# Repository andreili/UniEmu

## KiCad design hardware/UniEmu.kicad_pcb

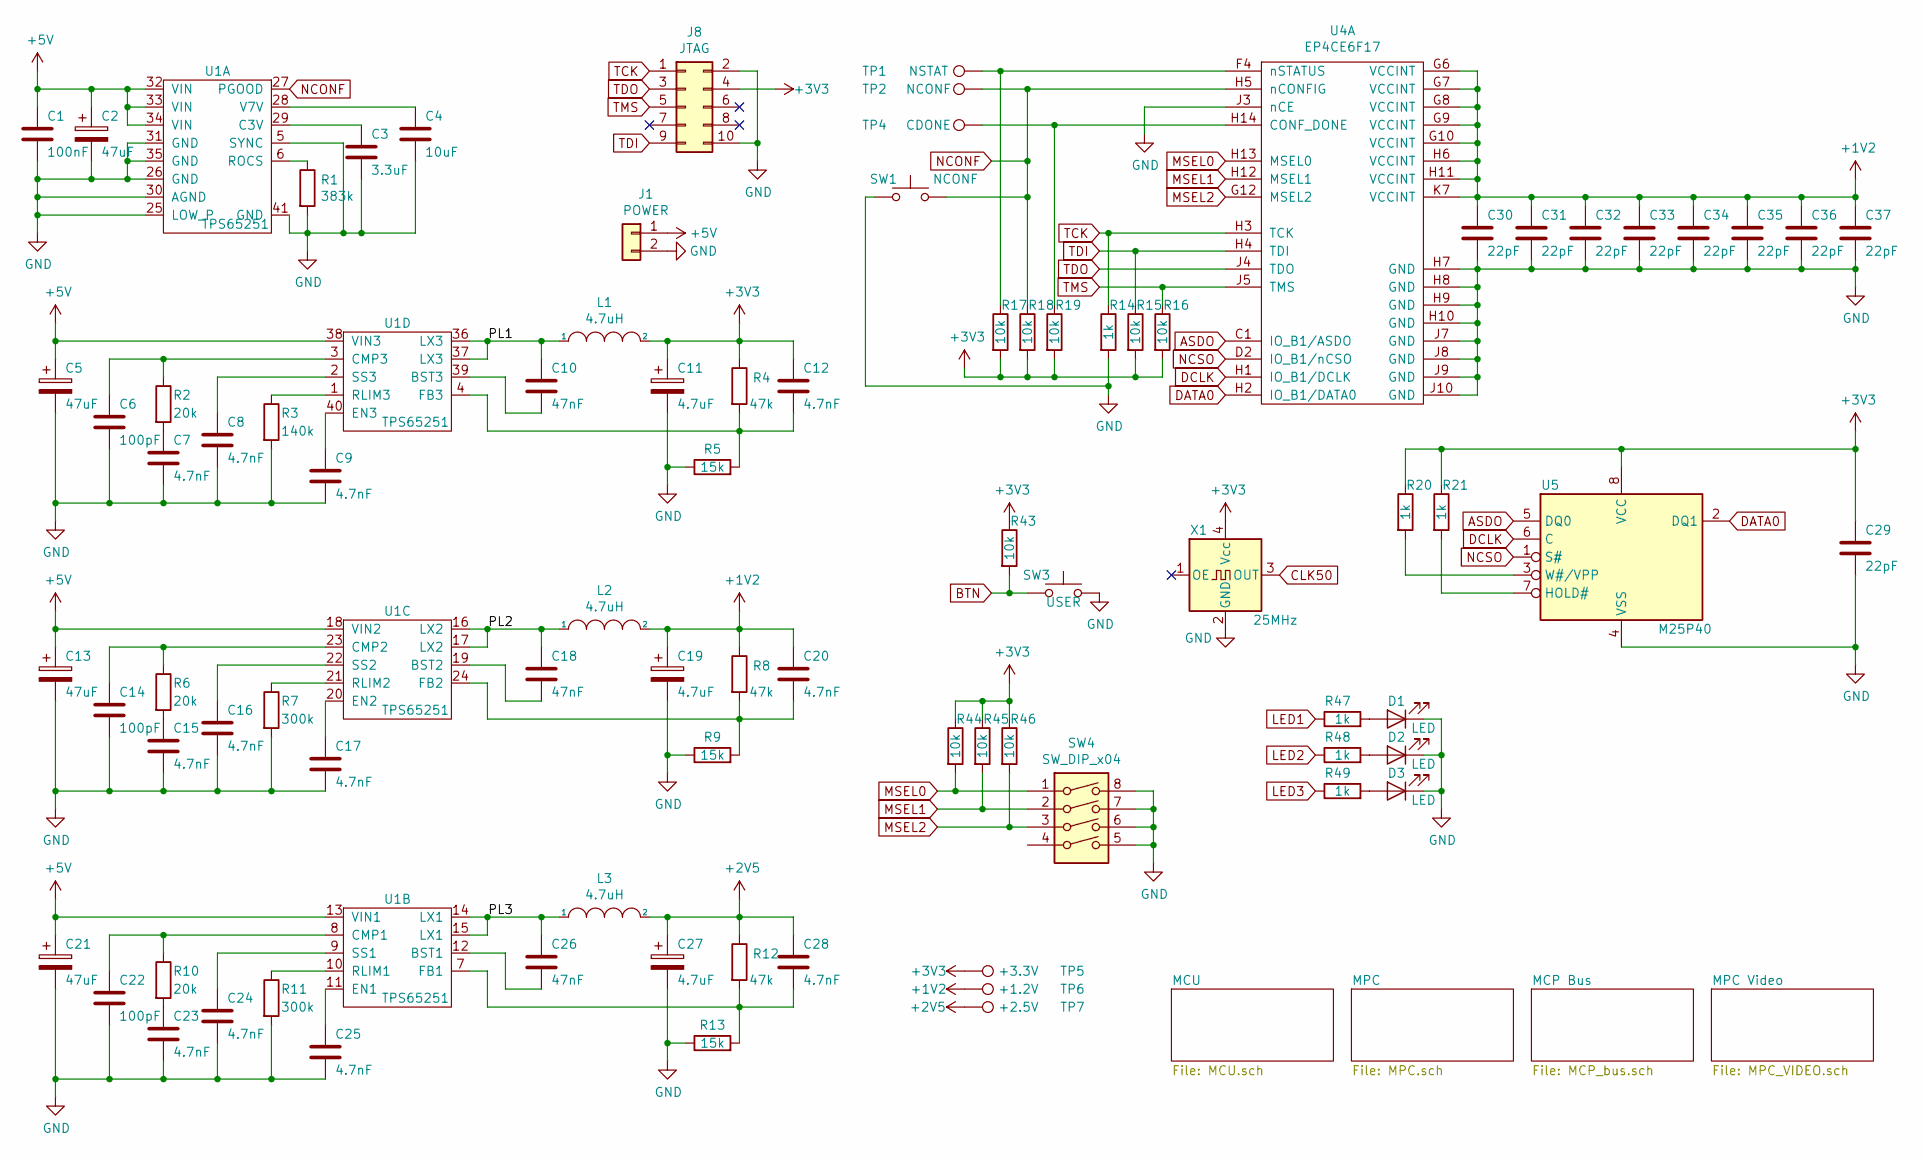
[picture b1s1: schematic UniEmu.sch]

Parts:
C1: 100nF; C_0805_2012Metric
C2, C5, C13, C21: 47uF; CP_EIA-3528-12_Kemet-T
C3: 3.3uF; C_0805_2012Metric
C4: 10uF; C_1206_3216Metric_Pad1.42x1.75mm_HandSolder
C6, C14, C22: 100pF; C_0805_2012Metric
C7, C8, C9, C12, C15, C16, C17, C20, C23, C24, C25, C28: 4.7nF; C_0805_2012Metric
C10, C18, C26: 47nF; C_0805_2012Metric
C11, C19, C27: 4.7uF; C_0805_2012Metric
C29, C30, C31, C32, C33, C34, C35, C36, C37: 22pF; C_0805_2012Metric
D1, D2, D3: LED; LED_0805_2012Metric_Castellated
J1: POWER; BarrelJack_Horizontal
J8: JTAG; IDC-Header_2x05_P2.54mm_Vertical
L1: 4.7uH; L_TDK_VLF10040
L2, L3: 4.7uH; L_Taiyo-Yuden_MD-4040
R1: 383k; R_0805_2012Metric
R2, R6, R10: 20k; R_0805_2012Metric
R3: 140k; R_0805_2012Metric
R4, R8, R12: 47k; R_0805_2012Metric
R5, R9, R13: 15k; R_0805_2012Metric
R7, R11: 300k; R_0805_2012Metric
R14, R20, R21, R47, R48, R49: 1k; R_0805_2012Metric
R15, R16, R17, R18, R19, R43, R44, R45, R46: 10k; R_0805_2012Metric
SW1: NCONF; SW_SPST_CK_RS282G05A3
SW3: USER; SW_SPST_CK_RS282G05A3
SW4: SW_DIP_x04; SW_DIP_SPSTx04_Slide_6.7x11.72mm_W8.61mm_P2.54mm_LowProfile
TP1: NSTAT; TestPoint_Pad_D1.5mm
TP2: NCONF; TestPoint_Pad_D1.5mm
TP4: CDONE; TestPoint_Pad_D1.5mm
TP5: +3.3V; TestPoint_Pad_D1.5mm
TP6: +1.2V; TestPoint_Pad_D1.5mm
TP7: +2.5V; TestPoint_Pad_D1.5mm
U1: TPS65251; QFN-40-1EP_6x6mm_P0.5mm_EP4.6x4.6mm_ThermalVias
U4: EP4CE6F17; BGA-256_17.0x17.0mm_Layout16x16_P1.0mm_Ball0.5mm_Pad0.4mm_N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
U5: M25P40; SOIC-8_3.9x4.9mm_P1.27mm
X1: 25MHz; Crystal_SMD_7050-4Pin_7.0x5.0mm

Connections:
+1V2: C19.1, C20.1, C30.1, C31.1, C32.1, C33.1, C34.1, C35.1, C36.1, C37.1, L2.2, R8.1, TP6.1, U4.G6 (VCCINT), U4.G7 (VCCINT), U4.G8 (VCCINT), U4.G9 (VCCINT), U4.G10 (VCCINT), U4.H6 (VCCINT), U4.H11 (VCCINT), U4.K7 (VCCINT); also elsewhere on the board
+2V5: C27.1, C28.1, L3.2, R12.1, TP7.1; also elsewhere on the board
+5V: C1.1, C2.1, C5.1, C13.1, C21.1, J1.1, U1.13 (VIN1), U1.18 (VIN2), U1.32 (VIN), U1.33 (VIN), U1.34 (VIN), U1.38 (VIN3); also elsewhere on the board
/PL1: C10.1, L1.1, U1.36 (LX3), U1.37 (LX3)
/PL2: C18.1, L2.1, U1.16 (LX2), U1.17 (LX2)
/PL3: C26.1, L3.1, U1.14 (LX1), U1.15 (LX1)
ASDO: U4.C1 (IO_B1/ASDO), U5.5 (DQ0)
BTN: R43.2, SW3.1; also elsewhere on the board
CLK50: X1.3 (OUT); also elsewhere on the board
DATA0: U4.H2 (IO_B1/DATA0), U5.2 (DQ1)
DCLK: U4.H1 (IO_B1/DCLK), U5.6 (C)
GND: C1.2, C2.2, C3.2, C4.2, C5.2, C6.2, C7.2, C8.2, C9.2, C11.2, C13.2, C14.2, C15.2, C16.2, C17.2, C19.2, C21.2, C22.2, C23.2, C24.2, C25.2, C27.2, C29.2, C30.2, C31.2, C32.2, C33.2, C34.2, C35.2, C36.2, C37.2, D1.1 (K), D2.1 (K), D3.1 (K), J1.2, J8.2, J8.10, R1.2, R3.2, R5.1, R7.2, R9.1, R11.2, R13.1, R14.2, SW1.1, SW3.2, SW4.5, SW4.6, SW4.7, SW4.8, U1.5 (SYNC), U1.25 (LOW_P), U1.26 (GND), U1.30 (AGND), U1.31 (GND), U1.35 (GND), U1.41 (GND), U4.H7 (GND), U4.H8 (GND), U4.H9 (GND), U4.H10 (GND), U4.J3 (nCE), U4.J7 (GND), U4.J8 (GND), U4.J9 (GND), U4.J10 (GND), U5.4 (VSS), X1.2 (GND); also elsewhere on the board
LED1: R47.1; also elsewhere on the board
LED2: R48.1; also elsewhere on the board
LED3: R49.1; also elsewhere on the board
MSEL0: R44.2, SW4.1, U4.H13 (MSEL0)
MSEL1: R45.2, SW4.2, U4.H12 (MSEL1)
MSEL2: R46.2, SW4.3, U4.G12 (MSEL2)
NCONF: R18.1, SW1.2, TP2.1, U1.27 (PGOOD), U4.H5 (nCONFIG)
NCSO: U4.D2 (IO_B1/nCSO), U5.1 (S#)
unnamed: C3.1, U1.29 (C3V)
unnamed: C4.1, U1.28 (V7V)
unnamed: C6.1, R2.1, U1.3 (CMP3)
unnamed: C7.1, R2.2
unnamed: C8.1, U1.2 (SS3)
unnamed: C9.1, U1.40 (EN3)
unnamed: C10.2, U1.39 (BST3)
unnamed: C12.2, R4.2, R5.2, U1.4 (FB3)
unnamed: C14.1, R6.1, U1.23 (CMP2)
unnamed: C15.1, R6.2
unnamed: C16.1, U1.22 (SS2)
unnamed: C17.1, U1.20 (EN2)
unnamed: C18.2, U1.19 (BST2)
unnamed: C20.2, R8.2, R9.2, U1.24 (FB2)
unnamed: C22.1, R10.1, U1.8 (CMP1)
unnamed: C23.1, R10.2
unnamed: C24.1, U1.9 (SS1)
unnamed: C25.1, U1.11 (EN1)
unnamed: C26.2, U1.12 (BST1)
unnamed: C28.2, R12.2, R13.2, U1.7 (FB1)
unnamed: D1.2 (A), R47.2
unnamed: D2.2 (A), R48.2
unnamed: D3.2 (A), R49.2
unnamed: R1.1, U1.6 (ROCS)
unnamed: R3.1, U1.1 (RLIM3)
unnamed: R7.1, U1.21 (RLIM2)
unnamed: R11.1, U1.10 (RLIM1)
unnamed: R17.1, TP1.1, U4.F4 (nSTATUS)
unnamed: R19.1, TP4.1, U4.H14 (CONF_DONE)
unnamed: R20.2, U5.3 (W#/VPP)
unnamed: R21.2, U5.7 (HOLD#)
TCK: J8.1, R14.1, U4.H3 (TCK)
TDI: J8.9, R15.1, U4.H4 (TDI)
TDO: J8.3, U4.J4 (TDO)
TMS: J8.5, R16.1, U4.J5 (TMS)
VREF: C11.1, C12.1, C29.1, J8.4, L1.2, R4.1, R15.2, R16.2, R17.2, R18.2, R19.2, R20.1, R21.1, R43.1, R44.1, R45.1, R46.1, TP5.1, U5.8 (VCC), X1.4 (Vcc); also elsewhere on the board

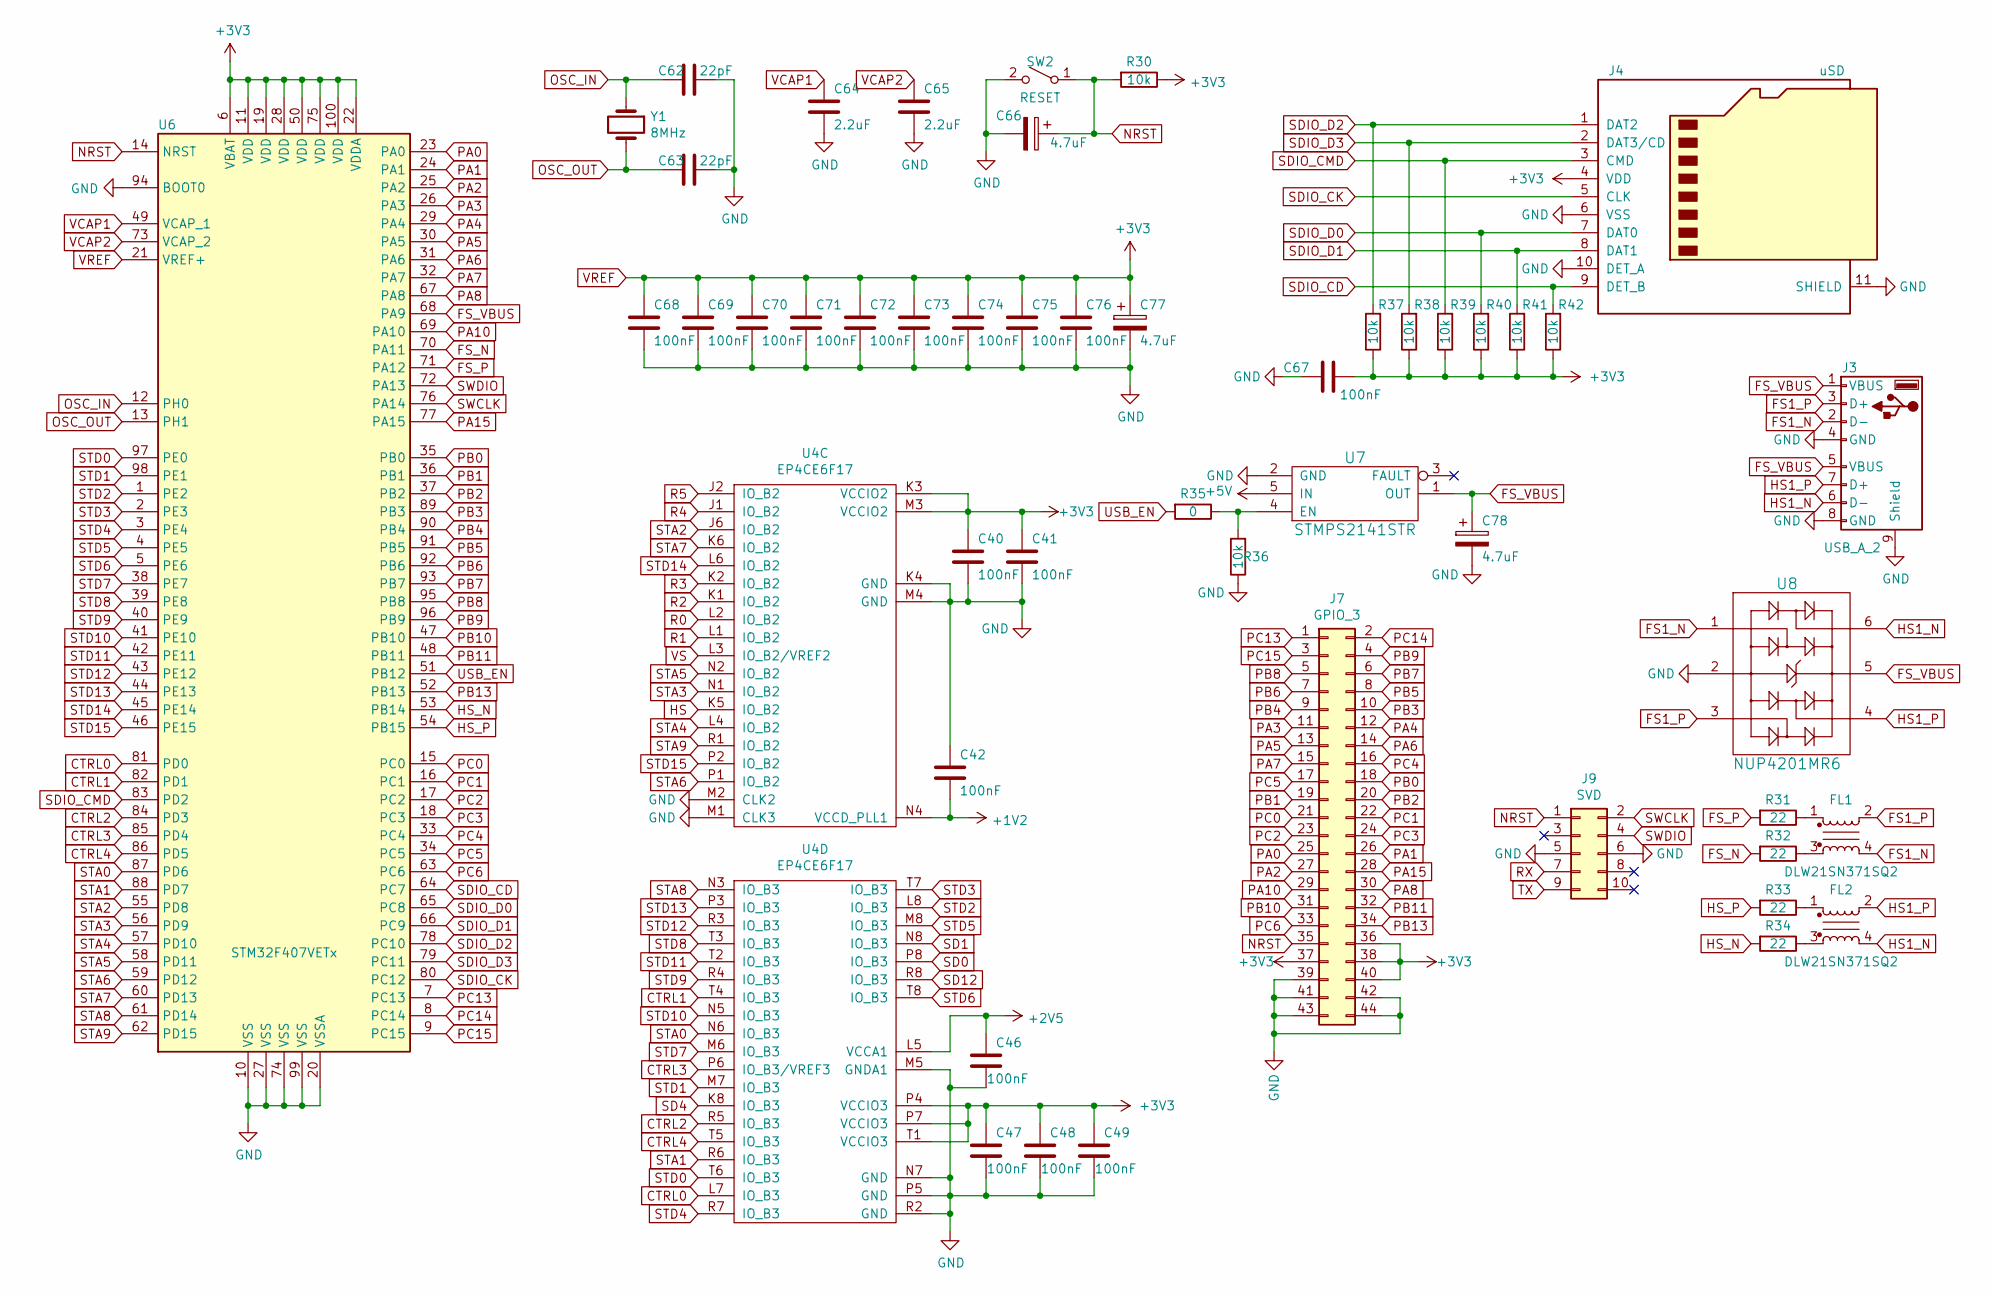
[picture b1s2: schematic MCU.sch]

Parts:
C40, C41, C42, C46, C47, C48, C49, C67, C68, C69, C70, C71, C72, C73, C74, C75, C76: 100nF; C_0805_2012Metric
C62, C63: 22pF; C_0805_2012Metric
C64, C65: 2.2uF; C_0805_2012Metric
C66: 4.7uF; CP_EIA-3216-18_Kemet-A
C77, C78: 4.7uF; CP_EIA-3528-12_Kemet-T
FL1, FL2: DLW21SN371SQ2; DLW21S
J3: USB_A_2; USB_A_Wuerth_61400826021_Horizontal_Stacked
J4: uSD; Conn_uSDcard
J7: GPIO_3; PinSocket_2x22_P2.00mm_Vertical
J9: SVD; IDC-Header_2x05_P2.54mm_Vertical
R30, R36, R37, R38, R39, R40, R41, R42: 10k; R_0805_2012Metric
R31, R32, R33, R34: 22; R_0402_1005Metric
R35: 0; R_0805_2012Metric
SW2: RESET; SW_Tactile_SPST_Angled_PTS645Vx39-2LFS
U4: EP4CE6F17; BGA-256_17.0x17.0mm_Layout16x16_P1.0mm_Ball0.5mm_Pad0.4mm_N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
U6: STM32F407VETx; LQFP-100_14x14mm_P0.5mm
U7: STMPS2141STR; SOT-23-5_HandSoldering
U8: NUP4201MR6; TSOP-6_1.65x3.05mm_P0.95mm
Y1: 8MHz; Crystal_SMD_5032-2Pin_5.0x3.2mm

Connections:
+1V2: C42.2, U4.N4 (VCCD_PLL1); also elsewhere on the board
+2V5: C46.1, U4.L5 (VCCA1); also elsewhere on the board
+5V: U7.5 (IN); also elsewhere on the board
CTRL0: U4.L7 (IO_B3), U6.81 (PD0)
CTRL1: U4.T4 (IO_B3), U6.82 (PD1)
CTRL2: U4.R5 (IO_B3), U6.84 (PD3)
CTRL3: U4.P6 (IO_B3/VREF3), U6.85 (PD4)
CTRL4: U4.T5 (IO_B3), U6.86 (PD5)
FS1_N: FL1.4, J3.2 (D-), U8.1
FS1_P: FL1.2, J3.3 (D+), U8.3
FS_N: R32.2, U6.70 (PA11)
FS_P: R31.2, U6.71 (PA12)
FS_VBUS: C78.1, J3.1 (VBUS), J3.5 (VBUS), U6.68 (PA9), U7.1 (OUT), U8.5
GND: C40.2, C41.2, C42.1, C46.2, C47.2, C48.2, C49.2, C62.1, C63.1, C64.2, C65.2, C66.2, C67.1, C68.2, C69.2, C70.2, C71.2, C72.2, C73.2, C74.2, C75.2, C76.2, C77.2, C78.2, J3.4 (GND), J3.8 (GND), J3.9 (Shield), J4.6 (VSS), J4.10 (DET_A), J4.11 (SHIELD), J7.39, J7.41, J7.42, J7.43, J7.44, J9.5, J9.6, R36.1, SW2.2 (B), U4.K4 (GND), U4.M1 (CLK3), U4.M2 (CLK2), U4.M4 (GND), U4.M5 (GNDA1), U4.N7 (GND), U4.P5 (GND), U4.R2 (GND), U6.10 (VSS), U6.20 (VSSA), U6.27 (VSS), U6.74 (VSS), U6.94 (BOOT0), U6.99 (VSS), U7.2 (GND), U8.2; also elsewhere on the board
HS: U4.K5 (IO_B2); also elsewhere on the board
HS1_N: FL2.4, J3.6 (D-), U8.6
HS1_P: FL2.2, J3.7 (D+), U8.4
HS_N: R34.2, U6.53 (PB14)
HS_P: R33.2, U6.54 (PB15)
NRST: C66.1, J7.35, J9.1, R30.2, SW2.1 (A), U6.14 (NRST)
unnamed: FL1.1, R31.1
unnamed: FL1.3, R32.1
unnamed: FL2.1, R33.1
unnamed: FL2.3, R34.1
unnamed: R35.1, R36.2, U7.4 (EN)
OSC_IN: C62.2, U6.12 (PH0), Y1.1
OSC_OUT: C63.2, U6.13 (PH1), Y1.2
PA0: J7.25, U6.23 (PA0)
PA1: J7.26, U6.24 (PA1)
PA2: J7.27, U6.25 (PA2)
PA3: J7.11, U6.26 (PA3)
PA4: J7.12, U6.29 (PA4)
PA5: J7.13, U6.30 (PA5)
PA6: J7.14, U6.31 (PA6)
PA7: J7.15, U6.32 (PA7)
PA8: J7.30, U6.67 (PA8)
PA10: J7.29, U6.69 (PA10)
PA15: J7.28, U6.77 (PA15)
PB0: J7.18, U6.35 (PB0)
PB1: J7.19, U6.36 (PB1)
PB2: J7.20, U6.37 (PB2)
PB3: J7.10, U6.89 (PB3)
PB4: J7.9, U6.90 (PB4)
PB5: J7.8, U6.91 (PB5)
PB6: J7.7, U6.92 (PB6)
PB7: J7.6, U6.93 (PB7)
PB8: J7.5, U6.95 (PB8)
PB9: J7.4, U6.96 (PB9)
PB10: J7.31, U6.47 (PB10)
PB11: J7.32, U6.48 (PB11)
PB13: J7.34, U6.52 (PB13)
PC0: J7.21, U6.15 (PC0)
PC1: J7.22, U6.16 (PC1)
PC2: J7.23, U6.17 (PC2)
PC3: J7.24, U6.18 (PC3)
PC4: J7.16, U6.33 (PC4)
PC5: J7.17, U6.34 (PC5)
PC6: J7.33, U6.63 (PC6)
PC13: J7.1, U6.7 (PC13)
PC14: J7.2, U6.8 (PC14)
PC15: J7.3, U6.9 (PC15)
R0: U4.L2 (IO_B2); also elsewhere on the board
R1: U4.L1 (IO_B2); also elsewhere on the board
R2: U4.K1 (IO_B2); also elsewhere on the board
R3: U4.K2 (IO_B2); also elsewhere on the board
R4: U4.J1 (IO_B2); also elsewhere on the board
R5: U4.J2 (IO_B2); also elsewhere on the board
RX: J9.7
SD0: U4.P8 (IO_B3); also elsewhere on the board
SD1: U4.N8 (IO_B3); also elsewhere on the board
SD4: U4.K8 (IO_B3); also elsewhere on the board
SD12: U4.R8 (IO_B3); also elsewhere on the board
SDIO_CD: J4.9 (DET_B), R42.2, U6.64 (PC7)
SDIO_CK: J4.5 (CLK), U6.80 (PC12)
SDIO_CMD: J4.3 (CMD), R39.2, U6.83 (PD2)
SDIO_D0: J4.7 (DAT0), R40.2, U6.65 (PC8)
SDIO_D1: J4.8 (DAT1), R41.2, U6.66 (PC9)
SDIO_D2: J4.1 (DAT2), R37.2, U6.78 (PC10)
SDIO_D3: J4.2 (DAT3/CD), R38.2, U6.79 (PC11)
STA0: U4.N6 (IO_B3), U6.87 (PD6)
STA1: U4.R6 (IO_B3), U6.88 (PD7)
STA2: U4.J6 (IO_B2), U6.55 (PD8)
STA3: U4.N1 (IO_B2), U6.56 (PD9)
STA4: U4.L4 (IO_B2), U6.57 (PD10)
STA5: U4.N2 (IO_B2), U6.58 (PD11)
STA6: U4.P1 (IO_B2), U6.59 (PD12)
STA7: U4.K6 (IO_B2), U6.60 (PD13)
STA8: U4.N3 (IO_B3), U6.61 (PD14)
STA9: U4.R1 (IO_B2), U6.62 (PD15)
STD0: U4.T6 (IO_B3), U6.97 (PE0)
STD1: U4.M7 (IO_B3), U6.98 (PE1)
STD2: U4.L8 (IO_B3), U6.1 (PE2)
STD3: U4.T7 (IO_B3), U6.2 (PE3)
STD4: U4.R7 (IO_B3), U6.3 (PE4)
STD5: U4.M8 (IO_B3), U6.4 (PE5)
STD6: U4.T8 (IO_B3), U6.5 (PE6)
STD7: U4.M6 (IO_B3), U6.38 (PE7)
STD8: U4.T3 (IO_B3), U6.39 (PE8)
STD9: U4.R4 (IO_B3), U6.40 (PE9)
STD10: U4.N5 (IO_B3), U6.41 (PE10)
STD11: U4.T2 (IO_B3), U6.42 (PE11)
STD12: U4.R3 (IO_B3), U6.43 (PE12)
STD13: U4.P3 (IO_B3), U6.44 (PE13)
STD14: U4.L6 (IO_B2), U6.45 (PE14)
STD15: U4.P2 (IO_B2), U6.46 (PE15)
SWCLK: J9.2, U6.76 (PA14)
SWDIO: J9.4, U6.72 (PA13)
TX: J9.9
USB_EN: R35.2, U6.51 (PB12)
VCAP1: C64.1, U6.49 (VCAP_1)
VCAP2: C65.1, U6.73 (VCAP_2)
VREF: C40.1, C41.1, C47.1, C48.1, C49.1, C67.2, C68.1, C69.1, C70.1, C71.1, C72.1, C73.1, C74.1, C75.1, C76.1, C77.1, J4.4 (VDD), J7.36, J7.37, J7.38, J7.40, R30.1, R37.1, R38.1, R39.1, R40.1, R41.1, R42.1, U4.K3 (VCCIO2), U4.M3 (VCCIO2), U4.P4 (VCCIO3), U4.P7 (VCCIO3), U4.T1 (VCCIO3), U6.6 (VBAT), U6.11 (VDD), U6.19 (VDD), U6.21 (VREF+), U6.22 (VDDA), U6.28 (VDD), U6.50 (VDD), U6.75 (VDD), U6.100 (VDD); also elsewhere on the board
VS: U4.L3 (IO_B2/VREF2); also elsewhere on the board

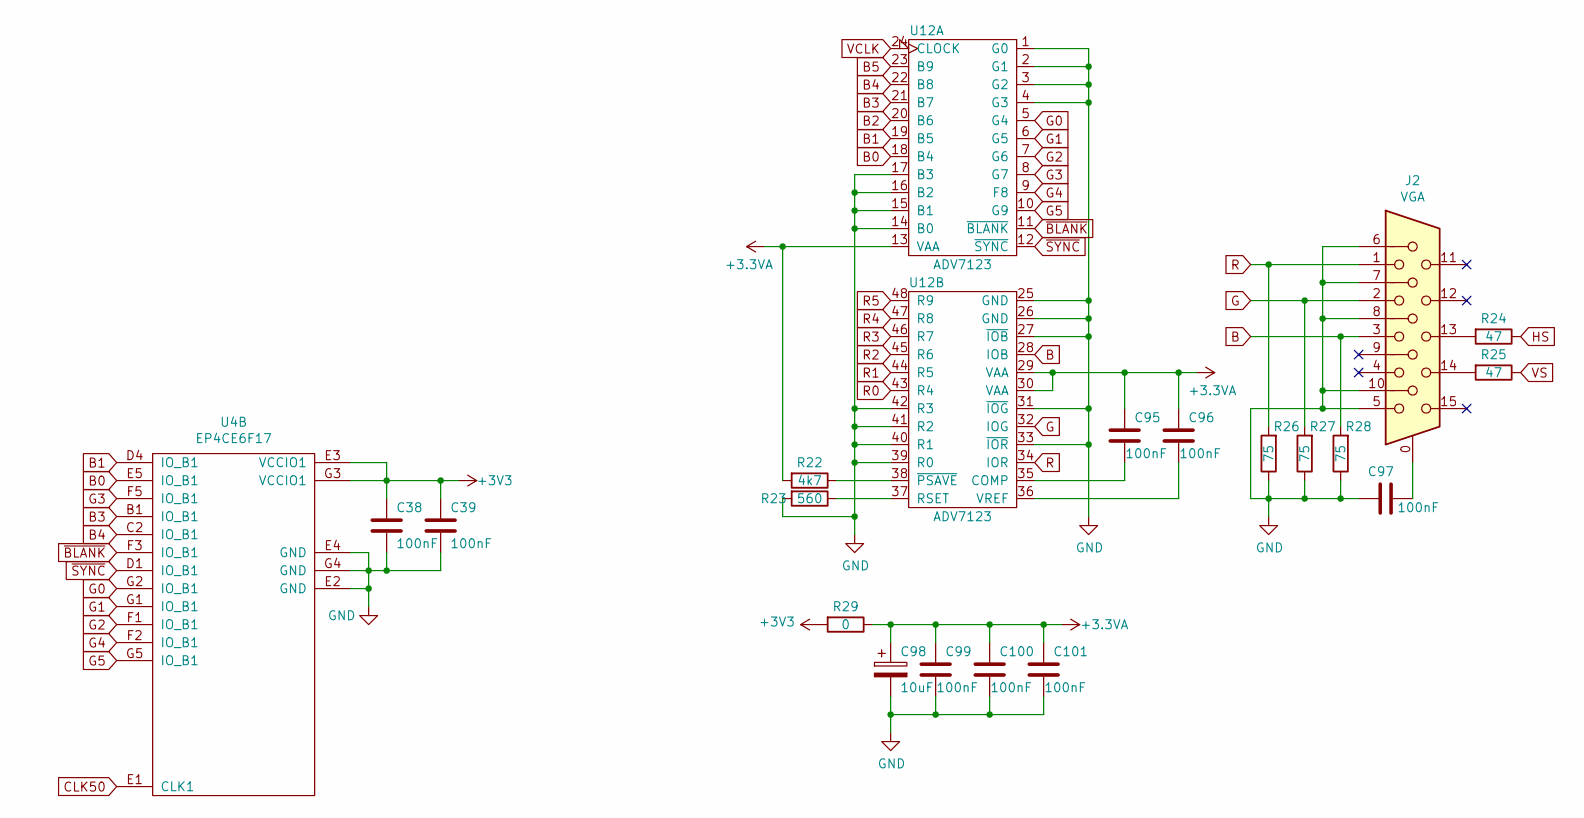
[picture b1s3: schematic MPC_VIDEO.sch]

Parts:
C38, C39, C95, C96, C97, C99, C100, C101: 100nF; C_0805_2012Metric
C98: 10uF; CP_EIA-3528-12_Kemet-T
J2: VGA; DSUB-15-HD_Female_Horizontal_P2.29x1.98mm_EdgePinOffset3.03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
R22: 4k7; R_0805_2012Metric
R23: 560; R_0805_2012Metric
R24, R25: 47; R_0805_2012Metric
R26, R27, R28: 75; R_0805_2012Metric
R29: 0; R_0805_2012Metric
U4: EP4CE6F17; BGA-256_17.0x17.0mm_Layout16x16_P1.0mm_Ball0.5mm_Pad0.4mm_N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
U12: ADV7123; LQFP-48_7x7mm_P0.5mm

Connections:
+3.3VA: C95.1, C96.1, C98.1, C99.1, C100.1, C101.1, R22.2, R29.1, U12.13 (VAA), U12.29 (VAA), U12.30 (VAA)
B: J2.3, R28.2, U12.28 (IOB)
B0: U4.E5 (IO_B1), U12.18 (B4)
B1: U4.D4 (IO_B1), U12.19 (B5)
B2: U12.20 (B6); also elsewhere on the board
B3: U4.B1 (IO_B1), U12.21 (B7)
B4: U4.C2 (IO_B1), U12.22 (B8)
B5: U12.23 (B9); also elsewhere on the board
CLK50: U4.E1 (CLK1); also elsewhere on the board
G: J2.2, R27.2, U12.32 (IOG)
G0: U4.G2 (IO_B1), U12.5 (G4)
G1: U4.G1 (IO_B1), U12.6 (G5)
G2: U4.F1 (IO_B1), U12.7 (G6)
G3: U4.F5 (IO_B1), U12.8 (G7)
G4: U4.F2 (IO_B1), U12.9 (F8)
G5: U4.G5 (IO_B1), U12.10 (G9)
GND: C38.2, C39.2, C97.1, C98.2, C99.2, C100.2, C101.2, J2.5, J2.6, J2.7, J2.8, J2.10, R23.2, R26.1, R27.1, R28.1, U4.E2 (GND), U4.E4 (GND), U4.G4 (GND), U12.1 (G0), U12.2 (G1), U12.3 (G2), U12.4 (G3), U12.14 (B0), U12.15 (B1), U12.16 (B2), U12.17 (B3), U12.25 (GND), U12.26 (GND), U12.27 (~IOB), U12.31 (~IOG), U12.33 (~IOR), U12.39 (R0), U12.40 (R1), U12.41 (R2), U12.42 (R3); also elsewhere on the board
HS: R24.1; also elsewhere on the board
unnamed: C95.2, U12.35 (COMP)
unnamed: C96.2, U12.36 (VREF)
unnamed: C97.2, J2.0
unnamed: J2.13, R24.2
unnamed: J2.14, R25.2
unnamed: R22.1, U12.38 (~PSAVE)
unnamed: R23.1, U12.37 (RSET)
R: J2.1, R26.2, U12.34 (IOR)
R0: U12.43 (R4); also elsewhere on the board
R1: U12.44 (R5); also elsewhere on the board
R2: U12.45 (R6); also elsewhere on the board
R3: U12.46 (R7); also elsewhere on the board
R4: U12.47 (R8); also elsewhere on the board
R5: U12.48 (R9); also elsewhere on the board
VCLK: U12.24 (CLOCK); also elsewhere on the board
VREF: C38.1, C39.1, R29.2, U4.E3 (VCCIO1), U4.G3 (VCCIO1); also elsewhere on the board
VS: R25.1; also elsewhere on the board
~BLANK: U4.F3 (IO_B1), U12.11 (~BLANK)
~SYNC: U4.D1 (IO_B1), U12.12 (~SYNC)

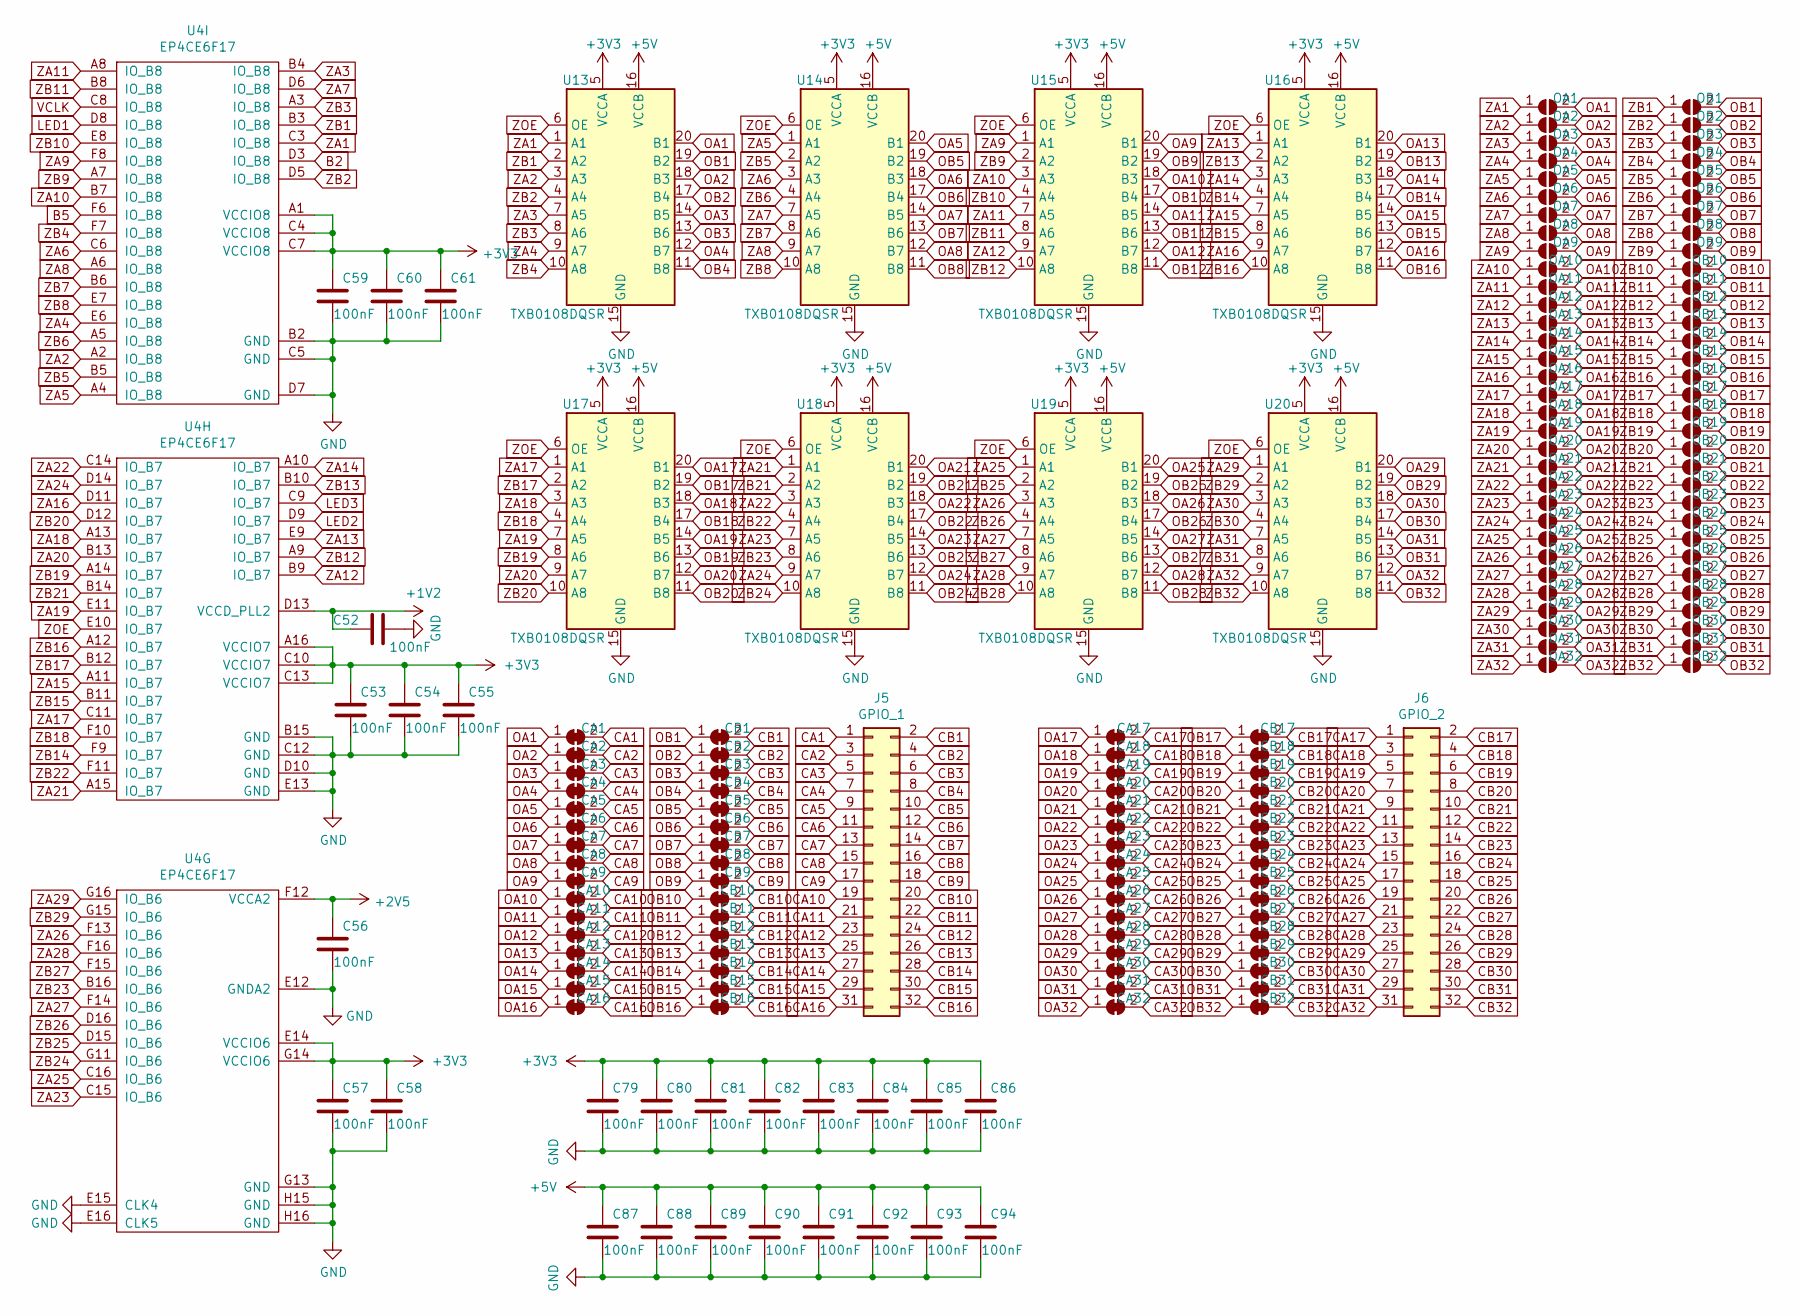
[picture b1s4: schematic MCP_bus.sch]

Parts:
C52, C53, C54, C55, C56, C57, C58, C59, C60, C61, C79, C80, C81, C82, C83, C84, C85, C86, C87, C88, C89, C90, C91, C92, C93, C94: 100nF; C_0805_2012Metric
CA1, CA2, CA3, CA4, CA5, CA6, CA7, CA8, CA9, CA10, CA11, CA12, CA13, CA14, CA15, CA16, CA17, CA18, CA19, CA20, CA21, CA22, CA23, CA24, CA25, CA26, CA27, CA28, CA29, CA30, CA31, CA32: SolderJumper_2_Bridged; SolderJumper-2_P1.3mm_Bridged_Pad1.0x1.5mm
CB1, CB2, CB3, CB4, CB5, CB6, CB7, CB8, CB9, CB10, CB11, CB12, CB13, CB14, CB15, CB16, CB17, CB18, CB19, CB20, CB21, CB22, CB23, CB24, CB25, CB26, CB27, CB28, CB29, CB30, CB31, CB32: SolderJumper_2_Bridged; SolderJumper-2_P1.3mm_Bridged_Pad1.0x1.5mm
J5: GPIO_1; PinHeader_2x16_P2.54mm_Vertical
J6: GPIO_2; PinHeader_2x16_P2.54mm_Vertical
OA1, OA2, OA3, OA4, OA5, OA6, OA7, OA8, OA9, OA10, OA11, OA12, OA13, OA14, OA15, OA16, OA17, OA18, OA19, OA20, OA21, OA22, OA23, OA24, OA25, OA26, OA27, OA28, OA29, OA30, OA31, OA32: OA1; SolderJumper-2_P0.4mm_Open_TrianglePad
OB1, OB2, OB3, OB4, OB5, OB6, OB7, OB8, OB9, OB10, OB11, OB12, OB13, OB14, OB15, OB16, OB17, OB18, OB19, OB20, OB21, OB22, OB23, OB24, OB25, OB26, OB27, OB28, OB29, OB30, OB31, OB32: OA1; SolderJumper-2_P0.4mm_Open_TrianglePad
U4: EP4CE6F17; BGA-256_17.0x17.0mm_Layout16x16_P1.0mm_Ball0.5mm_Pad0.4mm_N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
U13, U14, U15, U16, U17, U18, U19, U20: TXB0108DQSR; TSSOP-20_4.4x6.5mm_P0.65mm

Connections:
+1V2: C52.1, U4.D13 (VCCD_PLL2); also elsewhere on the board
+2V5: C56.1, U4.F12 (VCCA2); also elsewhere on the board
+5V: C87.1, C88.1, C89.1, C90.1, C91.1, C92.1, C93.1, C94.1, U13.16 (VCCB), U14.16 (VCCB), U15.16 (VCCB), U16.16 (VCCB), U17.16 (VCCB), U18.16 (VCCB), U19.16 (VCCB), U20.16 (VCCB); also elsewhere on the board
B2: U4.D3 (IO_B8); also elsewhere on the board
B5: U4.F6 (IO_B8); also elsewhere on the board
CA1: CA1.2 (B), J5.1
CA2: CA2.2 (B), J5.3
CA3: CA3.2 (B), J5.5
CA4: CA4.2 (B), J5.7
CA5: CA5.2 (B), J5.9
CA6: CA6.2 (B), J5.11
CA7: CA7.2 (B), J5.13
CA8: CA8.2 (B), J5.15
CA9: CA9.2 (B), J5.17
CA10: CA10.2 (B), J5.19
CA11: CA11.2 (B), J5.21
CA12: CA12.2 (B), J5.23
CA13: CA13.2 (B), J5.25
CA14: CA14.2 (B), J5.27
CA15: CA15.2 (B), J5.29
CA16: CA16.2 (B), J5.31
CA17: CA17.2 (B), J6.1
CA18: CA18.2 (B), J6.3
CA19: CA19.2 (B), J6.5
CA20: CA20.2 (B), J6.7
CA21: CA21.2 (B), J6.9
CA22: CA22.2 (B), J6.11
CA23: CA23.2 (B), J6.13
CA24: CA24.2 (B), J6.15
CA25: CA25.2 (B), J6.17
CA26: CA26.2 (B), J6.19
CA27: CA27.2 (B), J6.21
CA28: CA28.2 (B), J6.23
CA29: CA29.2 (B), J6.25
CA30: CA30.2 (B), J6.27
CA31: CA31.2 (B), J6.29
CA32: CA32.2 (B), J6.31
CB1: CB1.2 (B), J5.2
CB2: CB2.2 (B), J5.4
CB3: CB3.2 (B), J5.6
CB4: CB4.2 (B), J5.8
CB5: CB5.2 (B), J5.10
CB6: CB6.2 (B), J5.12
CB7: CB7.2 (B), J5.14
CB8: CB8.2 (B), J5.16
CB9: CB9.2 (B), J5.18
CB10: CB10.2 (B), J5.20
CB11: CB11.2 (B), J5.22
CB12: CB12.2 (B), J5.24
CB13: CB13.2 (B), J5.26
CB14: CB14.2 (B), J5.28
CB15: CB15.2 (B), J5.30
CB16: CB16.2 (B), J5.32
CB17: CB17.2 (B), J6.2
CB18: CB18.2 (B), J6.4
CB19: CB19.2 (B), J6.6
CB20: CB20.2 (B), J6.8
CB21: CB21.2 (B), J6.10
CB22: CB22.2 (B), J6.12
CB23: CB23.2 (B), J6.14
CB24: CB24.2 (B), J6.16
CB25: CB25.2 (B), J6.18
CB26: CB26.2 (B), J6.20
CB27: CB27.2 (B), J6.22
CB28: CB28.2 (B), J6.24
CB29: CB29.2 (B), J6.26
CB30: CB30.2 (B), J6.28
CB31: CB31.2 (B), J6.30
CB32: CB32.2 (B), J6.32
GND: C52.2, C53.2, C54.2, C55.2, C56.2, C57.2, C58.2, C59.2, C60.2, C61.2, C79.2, C80.2, C81.2, C82.2, C83.2, C84.2, C85.2, C86.2, C87.2, C88.2, C89.2, C90.2, C91.2, C92.2, C93.2, C94.2, U4.B2 (GND), U4.B15 (GND), U4.C5 (GND), U4.C12 (GND), U4.D7 (GND), U4.D10 (GND), U4.E12 (GNDA2), U4.E13 (GND), U4.E15 (CLK4), U4.E16 (CLK5), U4.G13 (GND), U4.H15 (GND), U4.H16 (GND), U13.15 (GND), U14.15 (GND), U15.15 (GND), U16.15 (GND), U17.15 (GND), U18.15 (GND), U19.15 (GND), U20.15 (GND); also elsewhere on the board
LED1: U4.D8 (IO_B8); also elsewhere on the board
LED2: U4.D9 (IO_B7); also elsewhere on the board
LED3: U4.C9 (IO_B7); also elsewhere on the board
OA1: CA1.1 (A), OA1.2 (B), U13.20 (B1)
OA2: CA2.1 (A), OA2.2 (B), U13.18 (B3)
OA3: CA3.1 (A), OA3.2 (B), U13.14 (B5)
OA4: CA4.1 (A), OA4.2 (B), U13.12 (B7)
OA5: CA5.1 (A), OA5.2 (B), U14.20 (B1)
OA6: CA6.1 (A), OA6.2 (B), U14.18 (B3)
OA7: CA7.1 (A), OA7.2 (B), U14.14 (B5)
OA8: CA8.1 (A), OA8.2 (B), U14.12 (B7)
OA9: CA9.1 (A), OA9.2 (B), U15.20 (B1)
OA10: CA10.1 (A), OA10.2 (B), U15.18 (B3)
OA11: CA11.1 (A), OA11.2 (B), U15.14 (B5)
OA12: CA12.1 (A), OA12.2 (B), U15.12 (B7)
OA13: CA13.1 (A), OA13.2 (B), U16.20 (B1)
OA14: CA14.1 (A), OA14.2 (B), U16.18 (B3)
OA15: CA15.1 (A), OA15.2 (B), U16.14 (B5)
OA16: CA16.1 (A), OA16.2 (B), U16.12 (B7)
OA17: CA17.1 (A), OA17.2 (B), U17.20 (B1)
OA18: CA18.1 (A), OA18.2 (B), U17.18 (B3)
OA19: CA19.1 (A), OA19.2 (B), U17.14 (B5)
OA20: CA20.1 (A), OA20.2 (B), U17.12 (B7)
OA21: CA21.1 (A), OA21.2 (B), U18.20 (B1)
OA22: CA22.1 (A), OA22.2 (B), U18.18 (B3)
OA23: CA23.1 (A), OA23.2 (B), U18.14 (B5)
OA24: CA24.1 (A), OA24.2 (B), U18.12 (B7)
OA25: CA25.1 (A), OA25.2 (B), U19.20 (B1)
OA26: CA26.1 (A), OA26.2 (B), U19.18 (B3)
OA27: CA27.1 (A), OA27.2 (B), U19.14 (B5)
OA28: CA28.1 (A), OA28.2 (B), U19.12 (B7)
OA29: CA29.1 (A), OA29.2 (B), U20.20 (B1)
OA30: CA30.1 (A), OA30.2 (B), U20.18 (B3)
OA31: CA31.1 (A), OA31.2 (B), U20.14 (B5)
OA32: CA32.1 (A), OA32.2 (B), U20.12 (B7)
OB1: CB1.1 (A), OB1.2 (B), U13.19 (B2)
OB2: CB2.1 (A), OB2.2 (B), U13.17 (B4)
OB3: CB3.1 (A), OB3.2 (B), U13.13 (B6)
OB4: CB4.1 (A), OB4.2 (B), U13.11 (B8)
OB5: CB5.1 (A), OB5.2 (B), U14.19 (B2)
OB6: CB6.1 (A), OB6.2 (B), U14.17 (B4)
OB7: CB7.1 (A), OB7.2 (B), U14.13 (B6)
OB8: CB8.1 (A), OB8.2 (B), U14.11 (B8)
OB9: CB9.1 (A), OB9.2 (B), U15.19 (B2)
OB10: CB10.1 (A), OB10.2 (B), U15.17 (B4)
OB11: CB11.1 (A), OB11.2 (B), U15.13 (B6)
OB12: CB12.1 (A), OB12.2 (B), U15.11 (B8)
OB13: CB13.1 (A), OB13.2 (B), U16.19 (B2)
OB14: CB14.1 (A), OB14.2 (B), U16.17 (B4)
OB15: CB15.1 (A), OB15.2 (B), U16.13 (B6)
OB16: CB16.1 (A), OB16.2 (B), U16.11 (B8)
OB17: CB17.1 (A), OB17.2 (B), U17.19 (B2)
OB18: CB18.1 (A), OB18.2 (B), U17.17 (B4)
OB19: CB19.1 (A), OB19.2 (B), U17.13 (B6)
OB20: CB20.1 (A), OB20.2 (B), U17.11 (B8)
OB21: CB21.1 (A), OB21.2 (B), U18.19 (B2)
OB22: CB22.1 (A), OB22.2 (B), U18.17 (B4)
OB23: CB23.1 (A), OB23.2 (B), U18.13 (B6)
OB24: CB24.1 (A), OB24.2 (B), U18.11 (B8)
OB25: CB25.1 (A), OB25.2 (B), U19.19 (B2)
OB26: CB26.1 (A), OB26.2 (B), U19.17 (B4)
OB27: CB27.1 (A), OB27.2 (B), U19.13 (B6)
OB28: CB28.1 (A), OB28.2 (B), U19.11 (B8)
OB29: CB29.1 (A), OB29.2 (B), U20.19 (B2)
OB30: CB30.1 (A), OB30.2 (B), U20.17 (B4)
OB31: CB31.1 (A), OB31.2 (B), U20.13 (B6)
OB32: CB32.1 (A), OB32.2 (B), U20.11 (B8)
VCLK: U4.C8 (IO_B8); also elsewhere on the board
VREF: C53.1, C54.1, C55.1, C57.1, C58.1, C59.1, C60.1, C61.1, C79.1, C80.1, C81.1, C82.1, C83.1, C84.1, C85.1, C86.1, U4.A1 (VCCIO8), U4.A16 (VCCIO7), U4.C4 (VCCIO8), U4.C7 (VCCIO8), U4.C10 (VCCIO7), U4.C13 (VCCIO7), U4.E14 (VCCIO6), U4.G14 (VCCIO6), U13.5 (VCCA), U14.5 (VCCA), U15.5 (VCCA), U16.5 (VCCA), U17.5 (VCCA), U18.5 (VCCA), U19.5 (VCCA), U20.5 (VCCA); also elsewhere on the board
ZA1: OA1.1 (A), U4.C3 (IO_B8), U13.1 (A1)
ZA2: OA2.1 (A), U4.A2 (IO_B8), U13.3 (A3)
ZA3: OA3.1 (A), U4.B4 (IO_B8), U13.7 (A5)
ZA4: OA4.1 (A), U4.E6 (IO_B8), U13.9 (A7)
ZA5: OA5.1 (A), U4.A4 (IO_B8), U14.1 (A1)
ZA6: OA6.1 (A), U4.C6 (IO_B8), U14.3 (A3)
ZA7: OA7.1 (A), U4.D6 (IO_B8), U14.7 (A5)
ZA8: OA8.1 (A), U4.A6 (IO_B8), U14.9 (A7)
ZA9: OA9.1 (A), U4.F8 (IO_B8), U15.1 (A1)
ZA10: OA10.1 (A), U4.B7 (IO_B8), U15.3 (A3)
ZA11: OA11.1 (A), U4.A8 (IO_B8), U15.7 (A5)
ZA12: OA12.1 (A), U4.B9 (IO_B7), U15.9 (A7)
ZA13: OA13.1 (A), U4.E9 (IO_B7), U16.1 (A1)
ZA14: OA14.1 (A), U4.A10 (IO_B7), U16.3 (A3)
ZA15: OA15.1 (A), U4.A11 (IO_B7), U16.7 (A5)
ZA16: OA16.1 (A), U4.D11 (IO_B7), U16.9 (A7)
ZA17: OA17.1 (A), U4.C11 (IO_B7), U17.1 (A1)
ZA18: OA18.1 (A), U4.A13 (IO_B7), U17.3 (A3)
ZA19: OA19.1 (A), U4.E11 (IO_B7), U17.7 (A5)
ZA20: OA20.1 (A), U4.B13 (IO_B7), U17.9 (A7)
ZA21: OA21.1 (A), U4.A15 (IO_B7), U18.1 (A1)
ZA22: OA22.1 (A), U4.C14 (IO_B7), U18.3 (A3)
ZA23: OA23.1 (A), U4.C15 (IO_B6), U18.7 (A5)
ZA24: OA24.1 (A), U4.D14 (IO_B7), U18.9 (A7)
ZA25: OA25.1 (A), U4.C16 (IO_B6), U19.1 (A1)
ZA26: OA26.1 (A), U4.F13 (IO_B6), U19.3 (A3)
ZA27: OA27.1 (A), U4.F14 (IO_B6), U19.7 (A5)
ZA28: OA28.1 (A), U4.F16 (IO_B6), U19.9 (A7)
ZA29: OA29.1 (A), U4.G16 (IO_B6), U20.1 (A1)
ZA30: OA30.1 (A), U20.3 (A3); also elsewhere on the board
ZA31: OA31.1 (A), U20.7 (A5); also elsewhere on the board
ZA32: OA32.1 (A), U20.9 (A7); also elsewhere on the board
ZB1: OB1.1 (A), U4.B3 (IO_B8), U13.2 (A2)
ZB2: OB2.1 (A), U4.D5 (IO_B8), U13.4 (A4)
ZB3: OB3.1 (A), U4.A3 (IO_B8), U13.8 (A6)
ZB4: OB4.1 (A), U4.F7 (IO_B8), U13.10 (A8)
ZB5: OB5.1 (A), U4.B5 (IO_B8), U14.2 (A2)
ZB6: OB6.1 (A), U4.A5 (IO_B8), U14.4 (A4)
ZB7: OB7.1 (A), U4.B6 (IO_B8), U14.8 (A6)
ZB8: OB8.1 (A), U4.E7 (IO_B8), U14.10 (A8)
ZB9: OB9.1 (A), U4.A7 (IO_B8), U15.2 (A2)
ZB10: OB10.1 (A), U4.E8 (IO_B8), U15.4 (A4)
ZB11: OB11.1 (A), U4.B8 (IO_B8), U15.8 (A6)
ZB12: OB12.1 (A), U4.A9 (IO_B7), U15.10 (A8)
ZB13: OB13.1 (A), U4.B10 (IO_B7), U16.2 (A2)
ZB14: OB14.1 (A), U4.F9 (IO_B7), U16.4 (A4)
ZB15: OB15.1 (A), U4.B11 (IO_B7), U16.8 (A6)
ZB16: OB16.1 (A), U4.A12 (IO_B7), U16.10 (A8)
ZB17: OB17.1 (A), U4.B12 (IO_B7), U17.2 (A2)
ZB18: OB18.1 (A), U4.F10 (IO_B7), U17.4 (A4)
ZB19: OB19.1 (A), U4.A14 (IO_B7), U17.8 (A6)
ZB20: OB20.1 (A), U4.D12 (IO_B7), U17.10 (A8)
ZB21: OB21.1 (A), U4.B14 (IO_B7), U18.2 (A2)
ZB22: OB22.1 (A), U4.F11 (IO_B7), U18.4 (A4)
ZB23: OB23.1 (A), U4.B16 (IO_B6), U18.8 (A6)
ZB24: OB24.1 (A), U4.G11 (IO_B6), U18.10 (A8)
ZB25: OB25.1 (A), U4.D15 (IO_B6), U19.2 (A2)
ZB26: OB26.1 (A), U4.D16 (IO_B6), U19.4 (A4)
ZB27: OB27.1 (A), U4.F15 (IO_B6), U19.8 (A6)
ZB28: OB28.1 (A), U19.10 (A8); also elsewhere on the board
ZB29: OB29.1 (A), U4.G15 (IO_B6), U20.2 (A2)
ZB30: OB30.1 (A), U20.4 (A4); also elsewhere on the board
ZB31: OB31.1 (A), U20.8 (A6); also elsewhere on the board
ZB32: OB32.1 (A), U20.10 (A8); also elsewhere on the board
ZOE: U4.E10 (IO_B7), U13.6 (OE), U14.6 (OE), U15.6 (OE), U16.6 (OE), U17.6 (OE), U18.6 (OE), U19.6 (OE), U20.6 (OE)

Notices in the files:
FPGA/ORION-NG/orion.qsf:
Copyright (C) 2017  Intel Corporation. All rights reserved.
hardware/UniEmu.kicad_pcb:
andreil, ©2019
